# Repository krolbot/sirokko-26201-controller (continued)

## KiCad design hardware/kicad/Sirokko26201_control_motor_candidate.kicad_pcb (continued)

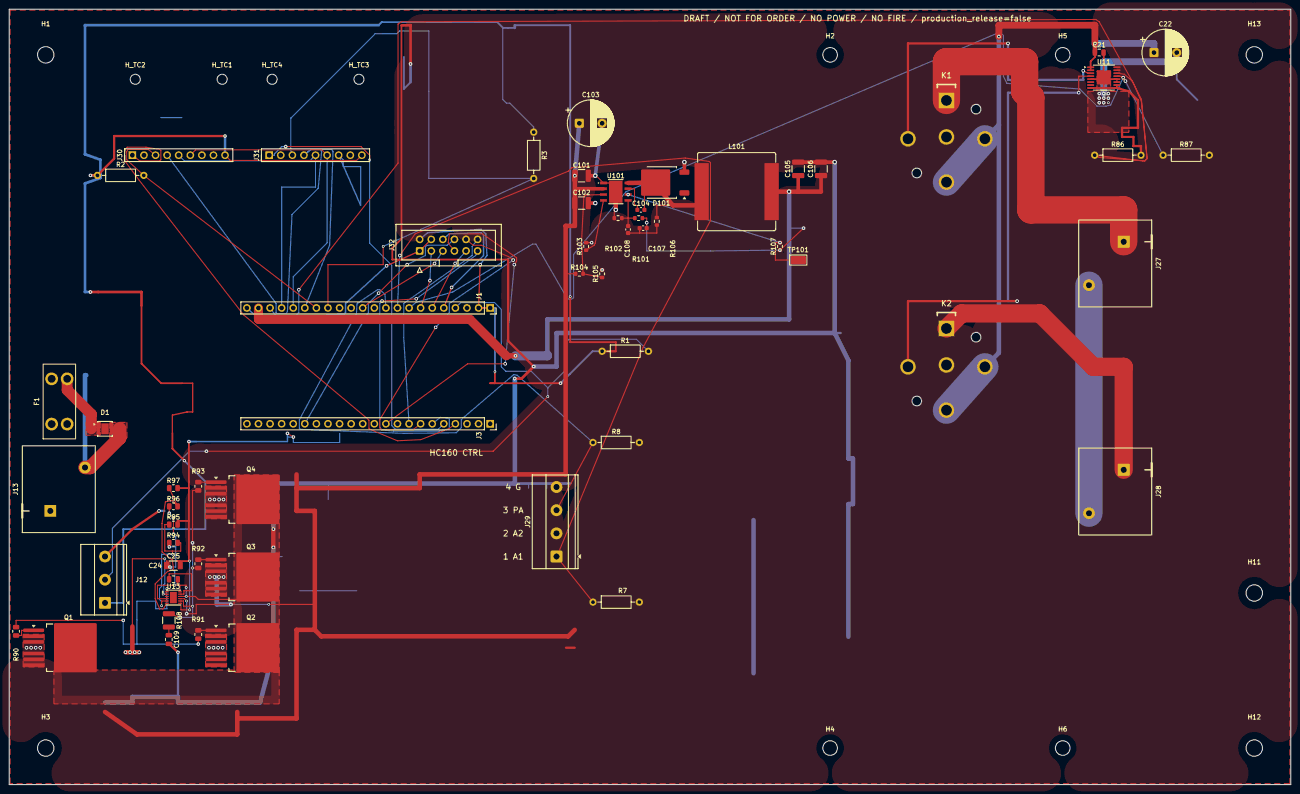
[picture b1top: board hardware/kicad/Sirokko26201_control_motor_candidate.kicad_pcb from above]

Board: 2 copper layers, 281.0 x 170.0 mm, 73 parts (0 on the bottom side), 49 nets.

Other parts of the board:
H1, H3, H11, H12, H13: MountingHole_3.6mm_R5.5_DRAFT
H2, H4: M3; MountingHole_3.2mm_M3
H5, H6: M3 SUPPORT; MountingHole_3.2mm_M3
H_TC1, H_TC2, H_TC3, H_TC4: MountingHole_2.2mm_M2

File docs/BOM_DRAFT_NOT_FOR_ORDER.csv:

"Refs","Value","Footprint","Qty","DNP"
"C21","100nF 100V X7R GRM21BR72A104KAC4L VM_BYPASS","Capacitor_SMD:C_0805_2012Metric","1",""
"C22","330uF 63V EEUFS1J331L BULK_DRAFT","Capacitor_THT:CP_Radial_D10.0mm_P5.00mm","1",""
"C24","220nF 100V X7R 10% CL21B224KCFSFNE","Capacitor_SMD:C_0805_2012Metric","1",""
"C25","1uF 100V CVS GRM31CR72A105KA01L","Sirokko_Capacitor:GRM31_1206_Murata_Reflow","1",""
"C101","2.2uF 100V X7R","Capacitor_SMD:C_1210_3225Metric","1",""
"C102","2.2uF 100V X7R","Capacitor_SMD:C_1210_3225Metric","1",""
"C103","100uF 100V EEU-FR2A101","Sirokko_Power:CP_Radial_D10.0mm_P5.00mm_Courtyard_D11.0mm","1",""
"C104","2.2nF 50V C0G 5%","Capacitor_SMD:C_0603_1608Metric","1",""
"C105","47uF 16V X5R","Capacitor_SMD:C_1210_3225Metric","1",""
"C106","47uF 16V X5R","Capacitor_SMD:C_1210_3225Metric","1",""
"C107","4.7nF 50V C0G","Capacitor_SMD:C_0603_1608Metric","1",""
"C108","820pF 50V C0G","Capacitor_SMD:C_0603_1608Metric","1",""
"C109","33nF 100V C0G 5% CdVdT WIP","Capacitor_SMD:C_0805_2012Metric","1",""
"D1","TVS3301DRBR WIP","Package_SON:VSON-8-1EP_3x3mm_P0.65mm_EP1.65x2.4mm","1",""
"D101","STPS5H100B-TR","Package_TO_SOT_SMD:TO-252-2","1",""
"F1","0997015.WXN / 15A","Sirokko_Input:Keystone_3568_MINI_Blade_3D_ENVELOPE","1",""
"J1","DEVKITC1_J1","Connector_PinSocket_2.54mm:PinSocket_1x22_P2.54mm_Vertical","1",""
"J3","DEVKITC1_J3","Connector_PinSocket_2.54mm:PinSocket_1x22_P2.54mm_Vertical","1",""
"J12","ROOM_DS18B20_HARNESS","TerminalBlock_Phoenix:TerminalBlock_Phoenix_MKDS-1,5-3-5.08_1x03_P5.08mm_Horizontal","1",""
"J13","24V_INPUT_PHOENIX_1756993_WIP","Sirokko_Power:Phoenix_1756993_MKDS5HV_2_9.52_ZSZS_3D_ENVELOPE","1",""
"J27","GLOW_OUTPUT_PHOENIX_1756993","Sirokko_Power:Phoenix_1756993_MKDS5HV_2_9.52_ZSZS_3D_ENVELOPE","1",""
"J28","CLUTCH_OUTPUT_PHOENIX_1756993","Sirokko_Power:Phoenix_1756993_MKDS5HV_2_9.52_ZSZS_3D_ENVELOPE","1",""
"J29","HC160_A1_A2_PA_G_CONTROL_ONLY","TerminalBlock_Phoenix:TerminalBlock_Phoenix_MKDS-1,5-4-5.08_1x04_P5.08mm_Horizontal","1",""
"J30","MAX31856 EXHAUST","Connector_Sirokko_Module:Samtec_SSW-109-01-T-S_1x09_P2.54mm_D1.04mm","1",""
"J31","MAX31856 AIR","Connector_Sirokko_Module:Samtec_SSW-109-01-T-S_1x09_P2.54mm_D1.04mm","1",""
"K1","DG85BM-5021-76-1024 + DZ85AB-5-PCB / GLOW","Sirokko_Relay_Mechanical:DZ85AB_5_PCB_DG85BM_ENVELOPE","1",""
"K2","DG85BM-5021-76-1024 + DZ85AB-5-PCB / CLUTCH_RUN","Sirokko_Relay_Mechanical:DZ85AB_5_PCB_DG85BM_ENVELOPE","1",""
"L101","33uH Isat>=10A","Inductor_SMD:L_Bourns_SRP1770TA_16.9x16.9mm","1",""
"Q1","IPB017N10N5LFATMA1 WIP","Sirokko_Input:Infineon_PG_TO263_7_IPB017N10N5LF","1",""
"Q2","IPB017N10N5LFATMA1 WIP","Sirokko_Input:Infineon_PG_TO263_7_IPB017N10N5LF","1",""
"Q3","IPB017N10N5LFATMA1 WIP","Sirokko_Input:Infineon_PG_TO263_7_IPB017N10N5LF","1",""
"Q4","IPB017N10N5LFATMA1 WIP","Sirokko_Input:Infineon_PG_TO263_7_IPB017N10N5LF","1",""
"R1","4k7","Resistor_THT:R_Axial_DIN0207_L6.3mm_D2.5mm_P10.16mm_Horizontal","1",""
"R2","10k","Resistor_THT:R_Axial_DIN0207_L6.3mm_D2.5mm_P10.16mm_Horizontal","1",""
"R3","10k","Resistor_THT:R_Axial_DIN0207_L6.3mm_D2.5mm_P10.16mm_Horizontal","1",""
"R7","10k","Resistor_THT:R_Axial_DIN0207_L6.3mm_D2.5mm_P10.16mm_Horizontal","1",""
"R8","10k","Resistor_THT:R_Axial_DIN0207_L6.3mm_D2.5mm_P10.16mm_Horizontal","1",""
"R86","4k7 DRV_IN1_PULLDOWN","Resistor_THT:R_Axial_DIN0207_L6.3mm_D2.5mm_P10.16mm_Horizontal","1",""
"R87","4k7 DRV_IN2_PULLDOWN","Resistor_THT:R_Axial_DIN0207_L6.3mm_D2.5mm_P10.16mm_Horizontal","1",""
"R90","4.7R Q1_GATE","Resistor_SMD:R_0805_2012Metric","1",""
"R91","4.7R Q2_GATE","Resistor_SMD:R_0805_2012Metric","1",""
"R92","4.7R Q3_GATE","Resistor_SMD:R_0805_2012Metric","1",""
"R93","4.7R Q4_GATE","Resistor_SMD:R_0805_2012Metric","1",""
"R94","84.5k 1% OV_TOP","Resistor_SMD:R_0805_2012Metric","1",""
"R95","3.48k 1% OV_BOT","Resistor_SMD:R_0805_2012Metric","1",""
"R96","75k 1% EN_TOP","Resistor_SMD:R_0805_2012Metric","1",""
"R97","5.62k 1% EN_BOT","Resistor_SMD:R_0805_2012Metric","1",""
"R101","31.6k 1%","Resistor_SMD:R_0603_1608Metric","1",""
"R102","10k 1%","Resistor_SMD:R_0603_1608Metric","1",""
"R103","31.6k 1%","Resistor_SMD:R_0603_1608Metric","1",""
"R104","100k 1%","Resistor_SMD:R_0603_1608Metric","1",""
"R105","10k 1%","Resistor_SMD:R_0603_1608Metric","1",""
"R106","82k 1%","Resistor_SMD:R_0603_1608Metric","1",""
"R107","10k 1%","Resistor_SMD:R_0603_1608Metric","1",""
"R108","22k 1% CdVdT isolation WIP","Resistor_SMD:R_1210_3225Metric","1",""
"TP101","PGOOD_5V_NOT_GPIO","TestPoint:TestPoint_Keystone_5015_Micro_Mini","1",""
"U11","DRV8803PWPR","Package_SO:HTSSOP-16-1EP_4.4x5mm_P0.65mm_EP3x3mm","1",""
"U13","LM74800QDRRRQ1 WIP_NOT_TRANSIENT_QUALIFIED","Package_SON:WSON-12-1EP_3x3mm_P0.5mm_EP1.5x2.5mm","1",""
"U101","LM5013DDAR","Sirokko_Power:DDA0008B_LM5013DDAR_TI4214849B_3D","1",""

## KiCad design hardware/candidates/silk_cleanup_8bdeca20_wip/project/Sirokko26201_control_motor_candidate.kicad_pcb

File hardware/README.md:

# Исходники платы

Откройте **[Sirokko.kicad_pro](Sirokko.kicad_pro)** в KiCad 10 со стандартными библиотеками. Локальные библиотеки подключены относительными путями.

- `Sirokko.kicad_pcb` — плата.
- `Sirokko.kicad_sch` — корневая схема, остальные `.kicad_sch` — её листы.
- `sym-lib-table`, `fp-lib-table`, `.kicad_sym`, `.pretty/`, `3dmodels/` — зависимости проекта с относительными путями.
- [schematic.pdf](schematic.pdf) — схема для просмотра без KiCad.

Производственные файлы находятся в [manufacturing](../manufacturing/). При изменении схемы или платы обновите соответствующие PDF, Gerber и монтажные ведомости.

[Сборка и подключения](../docs/assembly.md) · [Компоненты](BOM.md) · [Лицензии библиотек](KICAD_LIBRARIES_LICENSE.md)

## Вид платы

На изображениях — плата без вставных модулей. Часть компонентов показана габаритными моделями.

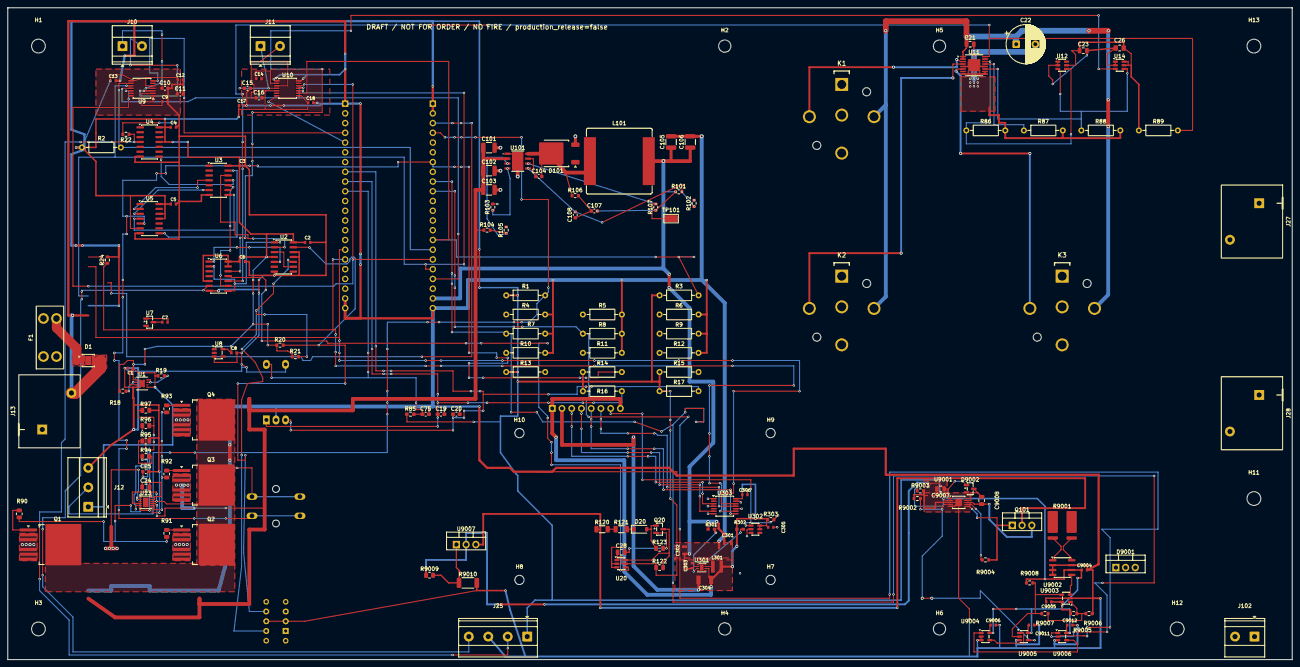
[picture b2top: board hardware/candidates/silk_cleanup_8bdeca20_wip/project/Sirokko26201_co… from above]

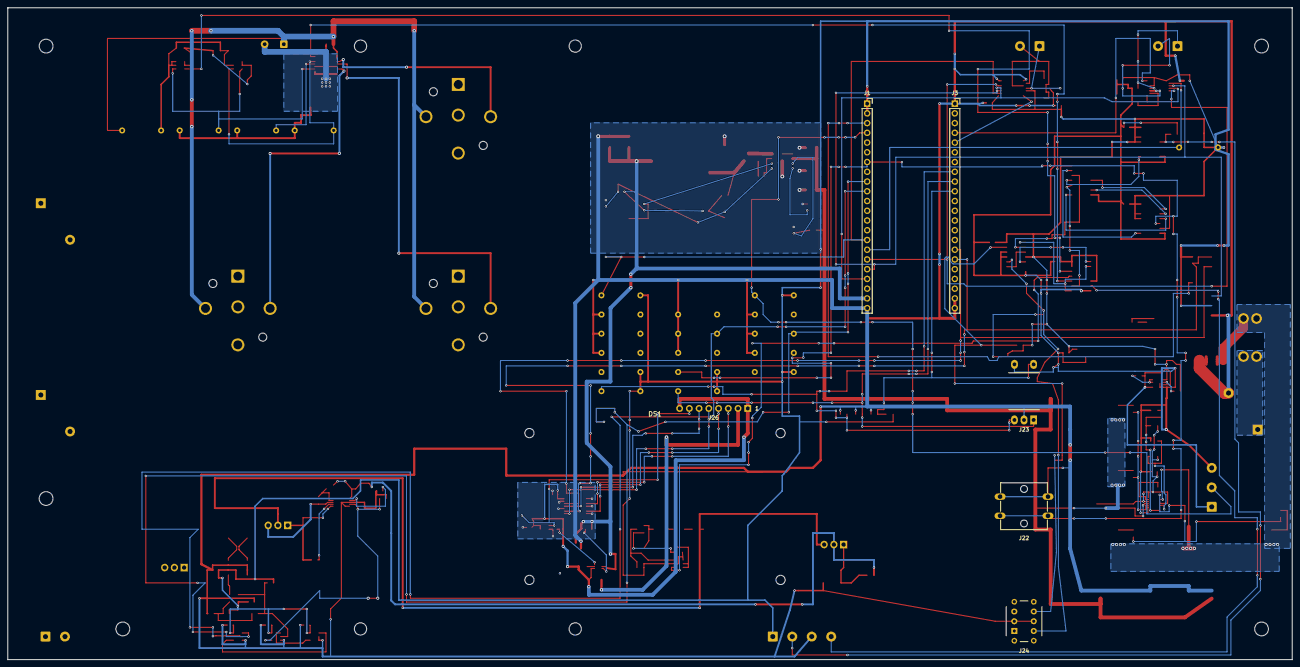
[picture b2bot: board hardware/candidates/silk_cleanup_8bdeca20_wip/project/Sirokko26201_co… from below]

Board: 2 copper layers, 335.0 x 170.0 mm, 181 parts (7 on the bottom side), 110 nets.

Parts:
C1, C2, C3, C4, C5, C6, C7, C8: 100n 16V X7R; C_Murata_GRM188_1608_Reflow
C9, C14: 0.1uF X7R 16V BIAS; C_Murata_GRM188_1608_Reflow
C10, C15: 0.01uF X7R 16V T+ filter; C_0603_1608Metric
C11, C16: 0.01uF X7R 16V T- filter; C_0603_1608Metric
C12, C17: 0.1uF X7R 16V AVDD; C_Murata_GRM188_1608_Reflow
C13, C18: 0.1uF X7R 16V DVDD; C_Murata_GRM188_1608_Reflow
C19: 10n ENC_A_FILTER; C_0603_1608Metric_Pad1.08x0.95mm_HandSolder
C20: 10n ENC_B_FILTER; C_0603_1608Metric_Pad1.08x0.95mm_HandSolder
C21: 100nF 100V X7R GRM21BR72A104KAC4L VM_BYPASS; C_0805_2012Metric
C22: 330uF 63V EEUFS1J331L BULK_DRAFT; CP_Radial_D10.0mm_P5.00mm
C23: 100nF 50V X7R U12_BYPASS; C_0805_2012Metric
C24: 220nF 100V CVCAP GRM21BR72A224KA01L; C_0805_2012Metric
C25: 100nF 100V CVS GRM188R72A104KA35D; C_0603_1608Metric
C26: 100nF 50V X7R U14_BYPASS; C_0805_2012Metric_Pad1.18x1.45mm_HandSolder
C28: 100nF 100V X7R 10% GRM21BR72A104KAC4L; C_0805_2012Metric
C75: 10n; C_0603_1608Metric_Pad1.08x0.95mm_HandSolder
C101, C102: 2.2uF 100V X7R; C_1210_3225Metric
C103: 22uF 100V BULK; C_1210_3225Metric
C104: 2.2nF 50V X7R; C_0603_1608Metric
C105, C106: 47uF 16V X7R; C_1210_3225Metric
C107: 4.7nF 50V C0G; C_0603_1608Metric
C108: 820pF 50V C0G; C_0603_1608Metric
C301, C302: 10uF GRM21BR61E106KA73L; C_Murata_GRM21B_2012_Reflow
C303: 100nF GRM188R71E104KA01D; C_Murata_GRM188_1608_Reflow
C304: 47uF GRM32ER61C476KE15L; C_Murata_GRM32E_3225_Reflow
C305, C306: 100nF; C_Murata_GRM188_1608_Reflow
C9004, C9005, C9006: 100nF X7R 16V; C_Murata_GRM188_1608_Reflow
C9007: 1uF ±10% X7R 50V 0805; LTC7001 VCC local decoupli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; C_0805_2012Metric
C9008: 1uF ±10% X7R 50V 0805 (BST-TS); C_0805_2012Metric
C9011: 100nF X7R 16V 10%; U9005 local bypass; C_Murata_GRM188_1608_Reflow
C9012: 100nF X7R 16V 10%; U9006 local bypass; C_Murata_GRM188_1608_Reflow
D1: TVS3301DRBR WIP; VSON-8-1EP_3x3mm_P0.65mm_EP1.65x2.4mm
D20: BZT52C15-7-F 15V 500mW; D_SOD-123
D101: STPS5H100B-TR; TO-252-2
D9001: STPS30H100CW; common cathode: K/pin2/tab -> MOTOR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; TO-220-3_Vertical
D9002: MMBD1501A; 200V 200mA silicon low-leakage bootstr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; SOT-23
DS1: Waveshare 18366 / 2.4inch LCD Module; Waveshare_18366_Module_Bside_Envelope_NO_CY
F1: 0997030.WXN / 30A WIP; Keystone_3568_MINI_Blade_3D_ENVELOPE
H1, H3, H11, H12, H13: MountingHole_3.6mm_R5.5_DRAFT
H2, H4: M3; MountingHole_3.2mm_M3
H5, H6: M3 SUPPORT; MountingHole_3.2mm_M3
H7, H8, H9, H10: WAVESHARE18366_M2_DRAFT_NOT_FOR_ORDER; MountingHole_2.4mm_M2_DRAFT
J1: DEVKITC1_J1; PinSocket_1x22_P2.54mm_Vertical
J3: DEVKITC1_J3; PinSocket_1x22_P2.54mm_Vertical
J10: TC_K_EXHAUST_T+_T-; TerminalBlock_Phoenix_MKDS-1,5-2-5.08_1x02_P5.08mm_Horizont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
J11: TC_K_AIR_T+_T-; TerminalBlock_Phoenix_MKDS-1,5-2-5.08_1x02_P5.08mm_Horizont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
J12: ROOM_DS18B20_HARNESS; TerminalBlock_Phoenix_MKDS-1,5-3-5.08_1x03_P5.08mm_Horizont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
J13: 24V_INPUT_PHOENIX_1756993_WIP; Phoenix_1756993_MKDS5HV_2_9.52_ZSZS_3D_ENVELOPE
J22: START_STOP B3F-4055 + B32-1380 RED; SW_SPST_Omron_B3F-40xx
J23: ENCODER EC11E15244G1 + KNOB 41001-1; RotaryEncoder_Alps_EC11E15244G1_Knob41001_3D_ENVELOPE
J24: RESET NKK BB25AB-FA; SW_NKK_BB25AB-FA_3D_ENVELOPE
J25: THERMAL_AND_HW_ENABLE_3V3_ONLY; TerminalBlock_Phoenix_MKDS-1,5-4-5.08_1x04_P5.08mm_Horizont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
J26: TFT CABLE HARWIN M20-9960845 RA THT; Harwin_M20_9960845_1x08_P2.54mm_RA_THT_Bside
J27: GLOW_OUTPUT_PHOENIX_1756993; Phoenix_1756993_MKDS5HV_2_9.52_ZSZS_3D_ENVELOPE
J28: CLUTCH_OUTPUT_PHOENIX_1756993; Phoenix_1756993_MKDS5HV_2_9.52_ZSZS_3D_ENVELOPE
J102: MOTOR_24V_HIGH_SPEED; 125W_HEATER_NAMEPLATE_NOT_M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; TerminalBlock_Phoenix_MKDS-1,5-2-5.08_1x02_P5.08mm_Horizont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
K1: DG85BM-5021-76-1024 + DZ85AB-5-PCB / GLOW; DZ85AB_5_PCB_DG85BM_ENVELOPE
K2: DG85BM-5021-76-1024 + DZ85AB-5-PCB / CLUTCH_RUN; DZ85AB_5_PCB_DG85BM_ENVELOPE
K3: DG85BM-5021-76-1024 + DZ85AB-5-PCB / CLUTCH_SAFE; DZ85AB_5_PCB_DG85BM_ENVELOPE
L101: 33uH Isat>=10A; L_Bourns_SRP1770TA_16.9x16.9mm
L301: 744025003 3.3uH; L_Wuerth_744025003_2828_Reflow
Q1, Q2, Q3, Q4: IPB017N10N5LFATMA1 WIP; Infineon_PG_TO263_7_IPB017N10N5LF
Q20: BC847B,215; SOT-23
Q101: IRFB4110PBF (100V; RDS(on) @ VGS=10V); TO-220-3_Vertical
R1: 4k7; R_Axial_DIN0207_L6.3mm_D2.5mm_P10.16mm_Horizontal
R2, R3, R4, R5, R6, R7, R8, R9, R10, R11, R12, R13, R14, R15: 10k; R_Axial_DIN0207_L6.3mm_D2.5mm_P10.16mm_Horizontal
R16: 2.2k ENC_A_PULLUP; R_Axial_DIN0207_L6.3mm_D2.5mm_P10.16mm_Horizontal
R17: 2.2k ENC_B_PULLUP; R_Axial_DIN0207_L6.3mm_D2.5mm_P10.16mm_Horizontal
R18, R19, R20, R21, R22, R102, R105, R107: 10k 1%; R_0603_1608Metric
R24: 10k TFT_CS_PULLUP; R_0603_1608Metric
R85: 2.2k; R_0603_1608Metric_Pad0.98x0.95mm_HandSolder
R86: 4k7 DRV_IN1_PULLDOWN; R_Axial_DIN0207_L6.3mm_D2.5mm_P10.16mm_Horizontal
R87: 4k7 DRV_IN2_PULLDOWN; R_Axial_DIN0207_L6.3mm_D2.5mm_P10.16mm_Horizontal
R88: 4k7 DRV_IN3_PULLDOWN; R_Axial_DIN0207_L6.3mm_D2.5mm_P10.16mm_Horizontal
R89: 10k RELAY_DRIVER_OK_PULLUP; R_Axial_DIN0207_L6.3mm_D2.5mm_P10.16mm_Horizontal
R90: 4.7R Q1_GATE; R_0805_2012Metric
R91: 4.7R Q2_GATE; R_0805_2012Metric
R92: 4.7R Q3_GATE; R_0805_2012Metric
R93: 4.7R Q4_GATE; R_0805_2012Metric
R94: 84.5k 1% OV_TOP; R_0805_2012Metric
R95: 3.48k 1% OV_BOT; R_0805_2012Metric
R96: 75k 1% EN_TOP; R_0805_2012Metric
R97: 5.62k 1% EN_BOT; R_0805_2012Metric
R101, R103: 31.6k 1%; R_0603_1608Metric
R104: 100k 1%; R_0603_1608Metric
R106: 82k 1%; R_0603_1608Metric
R120, R121: 2.7k 1% 0.25W RC1206FR-072K7L; R_1206_3216Metric
R122: 47k 1% 0.125W RC0805FR-0747KL; R_0805_2012Metric
R123: 100k 1% 0.125W RC0805FR-07100KL; R_0805_2012Metric
R301: 100k 1% EN; R_Yageo_RC0603_1608_Reflow
R302: 100k 1% PG; R_Yageo_RC0603_1608_Reflow
R303: 100k; R_0603_1608Metric
R9001: WSLP27262L000FEA; 2mOhm 1% 5W @70C; WSLP2726
R9002: 100k 1% gate-command pull-down; R_0603_1608Metric
R9003: 130k 1% (VCCUV ≈9.1V rising); R_0603_1608Metric
R9004: 10R gate turn-on damping; R_0603_1608Metric
R9005: 30.1k 1% OCP threshold high; R_0603_1608Metric
R9006: 10.0k 1% OCP threshold low; R_0603_1608Metric
R9007: 1.00M 1% OCP hysteresis feedback; R_0603_1608Metric
R9008: 10k 1% OCP_OK pull-up; R_0603_1608Metric
R9009: 75R 1% 0.125W; LM317 OUT→ADJ; R_0805_2012Metric
R9010: 681R 1% 0.75W; LM317 ADJ→GND; R_2010_5025Metric
TP101: PGOOD_5V_NOT_GPIO; TestPoint_Keystone_5015_Micro_Mini
U1: TPS3431SDRBR; TPS3431_DRB0008A_3D
U2: SN74HCS74D; SOIC-14_3.9x8.7mm_P1.27mm
U3: SN74HCS14D; SOIC-14_3.9x8.7mm_P1.27mm
U4, U5: SN74HCS30D; SOIC-14_3.9x8.7mm_P1.27mm
U6: SN74HCS11D; SOIC-14_3.9x8.7mm_P1.27mm
U7: TPS3839G33DBZR; SOT-23
U8: SN74LVC1G14DBVR; SOT-23-5
U9, U10: MAX31856MUD+; TSSOP-14_4.4x5mm_P0.65mm
U11: DRV8803PWPR; HTSSOP-16-1EP_4.4x5mm_P0.65mm_EP3x3mm
U12, U14, U20: SN74LVC1G97DBVR; SOT-23-6
U13: LM74800QDRRRQ1 WIP_NOT_TRANSIENT_QUALIFIED; WSON-12-1EP_3x3mm_P0.5mm_EP1.5x2.5mm
U101: LM5013DDAR; DDA0008B_LM5013DDAR_TI4214849B_3D
U301: TPS62162DSGR; Texas_DSG0008A_WSON-8-1EP_2x2mm_P0.5mm_EP0.9x1.6mm
U302: TPS3808G33DBVR; SOT-23-6
U303: 74LVC125APW,118 Nexperia ONLY; TSSOP-14_4.4x5mm_P0.65mm
U9001: LTC7001IMSE#PBF; MSOP-10 EP; MSOP-10-1EP_3x3mm_P0.5mm_EP1.68x1.88mm
U9002: INA240A1ID; SOIC-8_3.9x4.9mm_P1.27mm
U9003: TLV9020DBVR; SOT-23-5
U9004: SN74LVC1G32DBVR; SOT-23-5
U9005, U9006: SN74LVC1G08DBVR; SOT-23-5
U9007: LM317HVT/NOPB TO-220; TJ 0…125C; TO-220-3_Vertical

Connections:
+5V_DEVKIT: C105.1, C106.1, C107.2, C301.1, C302.1, C303.1, J1.21, L101.2, R101.1, R107.1, R301.1, U301.2
/+3V3: C1.1, C2.1, C3.1, C4.1, C5.1, C6.1, C7.1, C8.1, C12.1, C13.1, C17.1, C18.1, C23.1, C26.1, C28.1, C9004.1, C9005.1, C9006.1, C9011.1, C9012.1, J1.1, J1.2, J12.1, J25.1, R1.1, R2.1, R3.1, R13.1, R14.1, R15.1, R16.1, R17.1, R18.1, R19.1, R20.1, R21.1, R24.2, R85.1, R89.1, R122.1, R9005.1, R9008.1, U1.1, U1.3, U1.5, U2.4, U2.14, U3.14, U4.11, U4.12, U4.14, U5.6, U5.11, U5.12, U5.14, U6.5, U6.13, U6.14, U7.3, U8.5, U9.5, U9.8, U10.5, U10.8, U12.5, U14.5, U14.6, U20.1, U20.5, U9002.6, U9003.5, U9004.5, U9005.5, U9006.5
/ALLOW_LATCH: U2.5, U6.1
/ARM_READY: J3.7, R10.1, U4.5, U5.1
/CLEAR_OK: U2.1, U6.2, U6.8
/CLEAR_OK_BASE: U3.10, U6.9
/CLUTCH_STAGE1: K2.87, K3.30
/CLUTCH_SWITCHED_POS: J28.1, K3.87
/ENC_A: C19.1, J3.9, J23.1, R16.2
/ENC_B: C20.1, J3.8, J23.3, R17.2
/ENC_SW: C75.1, J3.10, J23.4, R85.2
/EXT_SAFETY_ENABLE: J25.4, U6.6
/FAN_REQUEST: J1.9, R7.1, U9006.1
/FUEL_CMD: J1.8, R5.1, R87.1, U3.3, U11.13
/FUEL_PERMIT: J3.18, R6.1, U3.5, U6.4
/GLOW_CMD: J1.20, R4.1, U3.9, U12.6
/GLOW_ENABLE_HW: R86.1, U11.14, U12.4
/GLOW_SWITCHED_POS: J27.1, K1.87
/GND: C1.2, C2.2, C3.2, C4.2, C5.2, C6.2, C7.2, C8.2, C9.2, C10.2, C11.2, C12.2, C13.2, C14.2, C15.2, C16.2, C17.2, C18.2, C19.2, C20.2, C21.2, C22.2, C23.2, C25.2, C26.2, C28.2, C75.2, C101.2, C102.2, C103.2, C105.2, C106.2, C301.2, C302.2, C303.2, C304.2, C305.2, C306.2, C9004.2, C9005.2, C9006.2, C9007.2, C9011.2, C9012.2, D1.5, D1.6, D1.7, D1.8, D101.3, D9001.1, D9001.3, J1.22, J3.1, J3.21, J3.22, J12.3, J13.2, J22.2, J23.2, J23.5, J24.2, J24.5, J25.3, J26.2, J27.2, J28.2, J102.2, Q20.2, R4.2, R5.2, R6.2, R7.2, R8.2, R9.2, R10.2, R11.2, R12.2, R22.2, R86.2, R87.2, R88.2, R95.2, R97.2, R102.2, R103.2, R105.2, R123.2, R9002.2, R9003.2, R9006.2, R9010.2, U1.4, U1.9, U2.7, U2.11, U2.12, U3.7, U4.7, U5.7, U6.7, U7.1, U8.3, U9.1, U9.14, U10.1, U10.14, U11.5, U11.8, U11.9, U11.10, U11.12, U11.17, U12.1, U12.2, U13.7, U14.1, U14.2, U20.2, U20.3, U101.1, U101.9, U301.1, U301.4, U301.5, U301.9, U302.2, U303.1, U303.4, U303.7, U303.10, U303.13, U9001.3, U9001.5, U9001.11, U9002.2, U9002.3, U9002.4, U9002.7, U9003.2, U9004.2, U9004.3, U9005.3, U9006.3
/HW_RESET_CLK: U2.3, U2.9
/INPUT_PROTECTION_WIP_NOT_QUALIFIED/CAP_NET: C24.1, U13.11
/INPUT_PROTECTION_WIP_NOT_QUALIFIED/DGATE: R90.1, R91.1, U13.1
/INPUT_PROTECTION_WIP_NOT_QUALIFIED/EN_DIV: R96.2, R97.1, U13.6
/INPUT_PROTECTION_WIP_NOT_QUALIFIED/HGATE: R92.1, R93.1, U13.8
/INPUT_PROTECTION_WIP_NOT_QUALIFIED/OV_DIV: R94.2, R95.1, U13.5
/INPUT_PROTECTION_WIP_NOT_QUALIFIED/Q1_GATE: Q1.1, R90.2
/INPUT_PROTECTION_WIP_NOT_QUALIFIED/Q2_GATE: Q2.1, R91.2
/INPUT_PROTECTION_WIP_NOT_QUALIFIED/Q3_GATE: Q3.1, R92.2
/INPUT_PROTECTION_WIP_NOT_QUALIFIED/Q4_GATE: Q4.1, R93.2
/INPUT_PROTECTION_WIP_NOT_QUALIFIED/REV_MID: C24.2, C25.1, Q1.4, Q2.4, Q3.4, Q4.4, R94.1, R96.1, U13.3, U13.4, U13.10, U13.12
/INPUT_PROTECTION_WIP_NOT_QUALIFIED/VIN_FUSED: D1.1, D1.2, D1.3, D1.4, F1.2, Q1.2, Q1.3, Q1.5, Q1.6, Q1.7, Q2.2, Q2.3, Q2.5, Q2.6, Q2.7, U13.2
/K_CLUTCH_RUN_COIL_LOW: K2.85, U11.4
/K_CLUTCH_SAFE_COIL_LOW: K3.85, U11.6
/K_GLOW_COIL_LOW: K1.85, U11.3
/LOGIC_POWER_24_TO_5V__DRAFT_NOT_FOR_ORDER/BOOT: C104.1, U101.7
/LOGIC_POWER_24_TO_5V__DRAFT_NOT_FOR_ORDER/EN_LOGIC: R104.2, R105.1, U101.3
/LOGIC_POWER_24_TO_5V__DRAFT_NOT_FOR_ORDER/FB: C108.2, R101.2, R102.1, U101.5
/LOGIC_POWER_24_TO_5V__DRAFT_NOT_FOR_ORDER/PGOOD_5V: R107.2, TP101.1, U101.6
/LOGIC_POWER_24_TO_5V__DRAFT_NOT_FOR_ORDER/RAMP: C107.1, C108.1, R106.2
/LOGIC_POWER_24_TO_5V__DRAFT_NOT_FOR_ORDER/RON: R103.1, U101.4
/LOGIC_POWER_24_TO_5V__DRAFT_NOT_FOR_ORDER/SW: C104.2, D101.2, L101.1, R106.1, U101.8
/MOTOR_PWM_REBUILD_CANDIDATE/BST: C9008.1, D9002.3, U9001.9
/MOTOR_PWM_REBUILD_CANDIDATE/FAN_REQUEST_OR_EMERG: U9004.4, U9005.1
/MOTOR_PWM_REBUILD_CANDIDATE/FAN_WORK_PWM: U9004.1, U9006.4
/MOTOR_PWM_REBUILD_CANDIDATE/GATE_Q101: Q101.1, R9004.2, U9001.6
/MOTOR_PWM_REBUILD_CANDIDATE/ISENSE_OUT: U9002.5, U9003.3
/MOTOR_PWM_REBUILD_CANDIDATE/MOTOR_GATE_CMD: R9002.1, U9001.4, U9005.4
/MOTOR_PWM_REBUILD_CANDIDATE/MOTOR_POS: D9001.2, J102.1, R9001.2, U9002.1
/MOTOR_PWM_REBUILD_CANDIDATE/OCP_OK: R9007.1, R9008.2, U9003.4, U9005.2
/MOTOR_PWM_REBUILD_CANDIDATE/OCP_THRESH: R9005.2, R9006.1, R9007.2, U9003.1
/MOTOR_PWM_REBUILD_CANDIDATE/SW_SHUNT_HI: C9008.2, Q101.3, R9001.1, U9001.8, U9002.8
/MOTOR_PWM_REBUILD_CANDIDATE/TGUP: R9004.1, U9001.7
/MOTOR_PWM_REBUILD_CANDIDATE/VADJ: R9009.2, R9010.1, U9007.1
/MOTOR_PWM_REBUILD_CANDIDATE/VCCUV: R9003.1, U9001.2
/MOTOR_PWM_REBUILD_CANDIDATE/VDRV12V: C9007.1, D9002.1, R9009.1, U9001.1, U9007.2
/NOT_CLEAR_OK: U3.11, U4.8
/NOT_FUEL_CMD: U3.4, U5.2
/NOT_FUEL_PERMIT: U3.6, U5.3
/NOT_GLOW_CMD: U3.8, U5.4
/NOT_RESET_ACCEPT: U3.13, U5.8
/NOT_SW_TRIP: U3.2, U4.6
/P24_BASE: D20.2, Q20.1, R123.1
/P24_PRESENT: U6.11, U20.4
/P24_PROTECTED: C21.1, C22.1, C101.1, C102.1, C103.1, K1.30, K1.86, K2.30, K2.86, K3.86, Q3.2, Q3.3, Q3.5, Q3.6, Q3.7, Q4.2, Q4.3, Q4.5, Q4.6, Q4.7, Q101.2, R104.1, R120.1, U11.1, U11.2, U13.9, U101.2, U9007.3
/P24_SENSE_N: Q20.3, R122.2, U20.6
/P24_SERIES_MID: R120.2, R121.1
/P24_ZENER_K: D20.1, R121.2
/PG_OK: U4.1, U7.2
/RELAY_DRIVER_OK: R89.2, U6.10, U11.16
/RESET_ACCEPT: U2.2, U3.12
/RESET_HW_NC_N: J24.6, R20.2, U2.13
/RESET_HW_NO_N: J24.4, R21.2, U2.10
/RESET_REQUEST: J1.6, J24.1, R13.2
/ROOM_DQ: J1.4, J12.2, R1.2
/SAFETY_OK: J1.5, R12.1, R88.1, U6.3, U11.11, U12.3, U14.4
/SAFETY_OK_RAW: U6.12, U14.3
/SPEED_CMD: J1.10, R8.1, U9006.2
/START_REQUEST: J1.7, J22.1, R14.2, U5.5
/STOP_OK: U4.3, U8.4
/STOP_STATUS: J1.12, R15.2, U8.2
/SW_TRIP: J3.6, R11.1, U3.1
/TC_AIR_BIAS: C14.1, U10.2
/TC_AIR_CS: J1.15, R3.2, U10.9
/TC_AIR_DRDY: J3.5, U10.7
/TC_AIR_TM: C16.1, J11.2, U10.3
/TC_AIR_TP: C15.1, J11.1, U10.4
/TC_EXH_BIAS: C9.1, U9.2
/TC_EXH_CS: J1.16, R2.2, U9.9
/TC_EXH_DRDY: J3.4, U9.7
/TC_EXH_TM: C11.1, J10.2, U9.3
/TC_EXH_TP: C10.1, J10.1, U9.4
/TC_SCK: J1.18, U9.10, U10.10, U303.5
/TC_SDI_MOSI: J1.17, U9.12, U10.12, U303.2
/TC_SDO_MISO: J1.19, U9.11, U10.11
/TFT_3V3: C304.1, C305.1, C306.1, J26.1, J26.8, L301.2, R302.1, R303.1, U301.6, U302.5, U302.6, U303.14
/TFT_CS: J3.17, R24.1, U303.9
/TFT_CS_BUF: J26.5, U303.8
/TFT_DC: J3.16, U303.12
/TFT_DC_BUF: J26.6, U303.11
/TFT_MOSI_BUF: J26.3, U303.3
/TFT_POWER_3V3_DRAFT/TFT_3V3_PG: R302.2, U301.8
/TFT_POWER_3V3_DRAFT/TFT_PWR_EN: R301.2, U301.3
/TFT_POWER_3V3_DRAFT/TFT_PWR_SW: L301.1, U301.7
/TFT_RESET_N: J26.7, R303.2, U302.1
/TFT_SCK_BUF: J26.4, U303.6
/THERMAL_OK: J25.2, R22.1, U4.4
/VIN_RAW_24: F1.1, J13.1
/WD_CWD_FIXED: R18.2, U1.2
/WD_HEARTBEAT: J1.11, R9.1, U1.6
/WD_OK: R19.2, U1.7, U1.8, U4.2

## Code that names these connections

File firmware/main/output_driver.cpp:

#include "output_driver.hpp"

#include <initializer_list>
#include "driver/gpio.h"
#include "driver/ledc.h"
#include "esp_log.h"

namespace {
constexpr gpio_num_t kGlow = GPIO_NUM_14;
constexpr gpio_num_t kMcuStopN = GPIO_NUM_8;
constexpr gpio_num_t kFuel = GPIO_NUM_15;
constexpr gpio_num_t kFan = GPIO_NUM_16;
constexpr gpio_num_t kSpeed = GPIO_NUM_17;
constexpr gpio_num_t kWatchdog = GPIO_NUM_18;
constexpr gpio_num_t kFuelPermit = GPIO_NUM_21;
constexpr gpio_num_t kArmReady = GPIO_NUM_41;
constexpr gpio_num_t kSoftwareTrip = GPIO_NUM_42;
}

bool OutputDriver::fail(esp_err_t error) {
    ready_ = false;
    arm_applied_ = stop_low_requested_ = false;
    applied_ = {};
    applied_.sw_trip = true;
    applied_speed_ = 0;
    // Do not short-circuit shutdown: attempt every independent inhibit on every failed pass.
    esp_err_t shutdown = ESP_OK;
    for (auto pin : {kFuel, kFuelPermit, kGlow, kArmReady, kWatchdog, kFan}) {
        shutdown |= gpio_set_level(pin, 0);
    }
    shutdown |= gpio_set_level(kSoftwareTrip, 1);
    shutdown |= gpio_set_level(kMcuStopN, 1); // Release OD, never push-pull HIGH.
    if (channel_configured_) shutdown |= ledc_stop(LEDC_LOW_SPEED_MODE, LEDC_CHANNEL_0, 0);
    // Disconnect GPIO17 from the LEDC matrix even if ledc_stop itself failed.
    shutdown |= gpio_reset_pin(kSpeed);
    shutdown |= gpio_set_level(kSpeed, 0);
    shutdown |= gpio_set_direction(kSpeed, GPIO_MODE_OUTPUT);
    shutdown_applied_ = shutdown == ESP_OK;
    if (!failure_reported_) {
        ESP_LOGE("outputs", "latched failure=%d shutdown=%d; reboot required", error, shutdown);
        failure_reported_ = true;
    }
    return false;
}

bool OutputDriver::initialize(const sirokko::Config& config) {
    if (started_) return fail(ESP_ERR_INVALID_STATE);
    started_ = true;
    gpio_config_t pins{};
    for (auto pin : {kGlow, kFuel, kFan, kSpeed, kWatchdog, kFuelPermit, kArmReady, kSoftwareTrip}) {
        pins.pin_bit_mask |= 1ULL << pin;
    }
    pins.mode = GPIO_MODE_OUTPUT;
    pins.pull_up_en = GPIO_PULLUP_DISABLE;
    pins.pull_down_en = GPIO_PULLDOWN_DISABLE;
    pins.intr_type = GPIO_INTR_DISABLE;
    // Stage safe levels before enabling any output, including active-HIGH SW_TRIP.
    esp_err_t error = ESP_OK;
    for (auto pin : {kFuel, kFuelPermit, kGlow, kFan, kSpeed, kWatchdog, kArmReady})
        error |= gpio_set_level(pin, 0);
    error |= gpio_set_level(kSoftwareTrip, 1);
    if (error != ESP_OK) return fail(error);
    error = gpio_config(&pins);
    if (error != ESP_OK) return fail(error);
    error = gpio_set_level(kMcuStopN, 1); // Preload released before enabling OD; no LOW pulse.
    if (error != ESP_OK) return fail(error);
    gpio_config_t stop{};
    stop.pin_bit_mask = 1ULL << kMcuStopN;
    stop.mode = GPIO_MODE_INPUT_OUTPUT_OD;
    stop.pull_up_en = GPIO_PULLUP_DISABLE; // External R15; reading must be the actual input pad.
    stop.pull_down_en = GPIO_PULLDOWN_DISABLE;
    stop.intr_type = GPIO_INTR_DISABLE;
    error = gpio_config(&stop);
    if (error != ESP_OK || gpio_get_level(kMcuStopN) != 1) return fail(ESP_FAIL);
    if (sirokko::validate_config(config) != sirokko::CONFIG_OK) return fail(ESP_ERR_INVALID_ARG);
    ledc_timer_config_t timer{};
    timer.speed_mode = LEDC_LOW_SPEED_MODE;
    timer.duty_resolution = LEDC_TIMER_10_BIT;
    timer.timer_num = LEDC_TIMER_0;
    timer.freq_hz = config.pwm_frequency_hz;
    timer.clk_cfg = LEDC_USE_APB_CLK;
    error = ledc_timer_config(&timer);
    if (error != ESP_OK) return fail(error);
    if (ledc_get_freq(LEDC_LOW_SPEED_MODE, LEDC_TIMER_0) == 0 ||
        ledc_get_freq(LEDC_LOW_SPEED_MODE, LEDC_TIMER_0) > sirokko::kPwmMaximumFrequencyHz) {
        return fail(ESP_ERR_INVALID_STATE);
    }
    ledc_channel_config_t channel{};
    channel.gpio_num = kSpeed;
    channel.speed_mode = LEDC_LOW_SPEED_MODE;
    channel.channel = LEDC_CHANNEL_0;
    channel.intr_type = LEDC_INTR_DISABLE;
    channel.timer_sel = LEDC_TIMER_0;
    channel.duty = 0;
    channel.hpoint = 0;
    // A failing channel_config may already have connected the matrix; fail() also detaches it.
    channel_configured_ = true;
    error = ledc_channel_config(&channel);
    if (error != ESP_OK) return fail(error);
    error = ledc_stop(LEDC_LOW_SPEED_MODE, LEDC_CHANNEL_0, 0);
    if (error != ESP_OK) return fail(error);
    ready_ = true;
    return true;
}

bool OutputDriver::set_speed(uint16_t permille) {
    if (!sirokko::speed_supported(permille)) return fail(ESP_ERR_INVALID_ARG);
    if (permille == applied_speed_) return true;
    esp_err_t error;
    if (permille == 0 || permille == 1000) {
        // ESP32-S3 / IDF 5.5.2 ledc_stop disables sig_out_en and selects constant idle level.
        error = ledc_stop(LEDC_LOW_SPEED_MODE, LEDC_CHANNEL_0, permille == 1000 ? 1 : 0);
    } else {
        const uint32_t duty = (static_cast<uint32_t>(permille) *
                               (1u << sirokko::kPwmResolutionBits) + 500u) / 1000u;
        error = ledc_set_duty(LEDC_LOW_SPEED_MODE, LEDC_CHANNEL_0, duty);
        // IDF update_duty enables sig_out_en again, only after the new duty was staged.
        if (error == ESP_OK) error = ledc_update_duty(LEDC_LOW_SPEED_MODE, LEDC_CHANNEL_0);
    }
    if (error != ESP_OK) return fail(error);
    applied_speed_ = permille;
    return true;
}

bool OutputDriver::apply(const sirokko::Outputs& out) {
    if (!ready_) return fail(ESP_ERR_INVALID_STATE);
    sirokko::Outputs next = out;
    if (!out.arm_ready || out.sw_trip) {
        // Remove independent enables before releasing GPIO8. HIGH here is intentional inhibit.
        esp_err_t inhibit = ESP_OK;
        for (auto pin : {kFuel, kFuelPermit, kGlow, kArmReady, kWatchdog}) inhibit |= gpio_set_level(pin, 0);
        inhibit |= gpio_set_level(kSoftwareTrip, 1);
        inhibit |= gpio_set_level(kMcuStopN, 1);
        stop_low_requested_ = arm_applied_ = false;
        if (inhibit != ESP_OK || gpio_get_level(kMcuStopN) != 1) return fail(ESP_FAIL);
        next.fuel_command = next.fuel_permit = next.glow_command = false;
        next.arm_ready = next.watchdog_heartbeat = false;
        next.sw_trip = true;
    } else if (!stop_low_requested_) {
        // First pass: request LOW while every independent enable is still inhibited.
        esp_err_t inhibit = ESP_OK;
        for (auto pin : {kFuel, kFuelPermit, kGlow, kArmReady, kWatchdog}) inhibit |= gpio_set_level(pin, 0);
        inhibit |= gpio_set_level(kSoftwareTrip, 1);
        if (inhibit != ESP_OK) return fail(inhibit);
        if (gpio_set_level(kMcuStopN, 0) != ESP_OK) return fail(ESP_FAIL);
        stop_low_requested_ = true;
        next.fuel_command = next.fuel_permit = next.glow_command = false;
        next.arm_ready = next.watchdog_heartbeat = false;
        next.sw_trip = true;
    } else {
        // A later control pass must freshly observe the real pad; never reuse a cached LOW.
        if (gpio_get_level(kMcuStopN) != 0) return fail(ESP_FAIL);
        arm_applied_ = true;
    }
    esp_err_t error = ESP_OK;
    if (!next.fuel_command || !next.fuel_permit) {
        error |= gpio_set_level(kFuel, 0);
        error |= gpio_set_level(kFuelPermit, 0);
    }
    if (error != ESP_OK) return fail(error);
    if (!next.glow_command && gpio_set_level(kGlow, 0) != ESP_OK) return fail(ESP_FAIL);
    if (!set_speed(next.speed_permille)) return false;
    error |= gpio_set_level(kGlow, next.glow_command ? 1 : 0);
    error |= gpio_set_level(kFan, next.fan_request ? 1 : 0);
    error |= gpio_set_level(kArmReady, next.arm_ready ? 1 : 0);
    error |= gpio_set_level(kSoftwareTrip, next.sw_trip ? 1 : 0);
    if (error != ESP_OK) return fail(error);
    if (next.fuel_command && next.fuel_permit && next.fan_request && next.arm_ready) {
        error = gpio_set_level(kFuelPermit, 1);
        if (error == ESP_OK) error = gpio_set_level(kFuel, 1);
    }
    if (error != ESP_OK) return fail(error);
    // Heartbeat is last: it must not certify an incomplete output pass.
    if (gpio_set_level(kWatchdog, next.watchdog_heartbeat ? 1 : 0) != ESP_OK) return fail(ESP_FAIL);
    applied_ = next;
    return true;
}
